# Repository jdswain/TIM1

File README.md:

# TIM1
Hardware files for 6504 based TIM-1 board.

This is a PCB for the Rockwell or MOS TIM-1 system.

More information can be found on <a href="https://swain.nz/micro">my website.</a>

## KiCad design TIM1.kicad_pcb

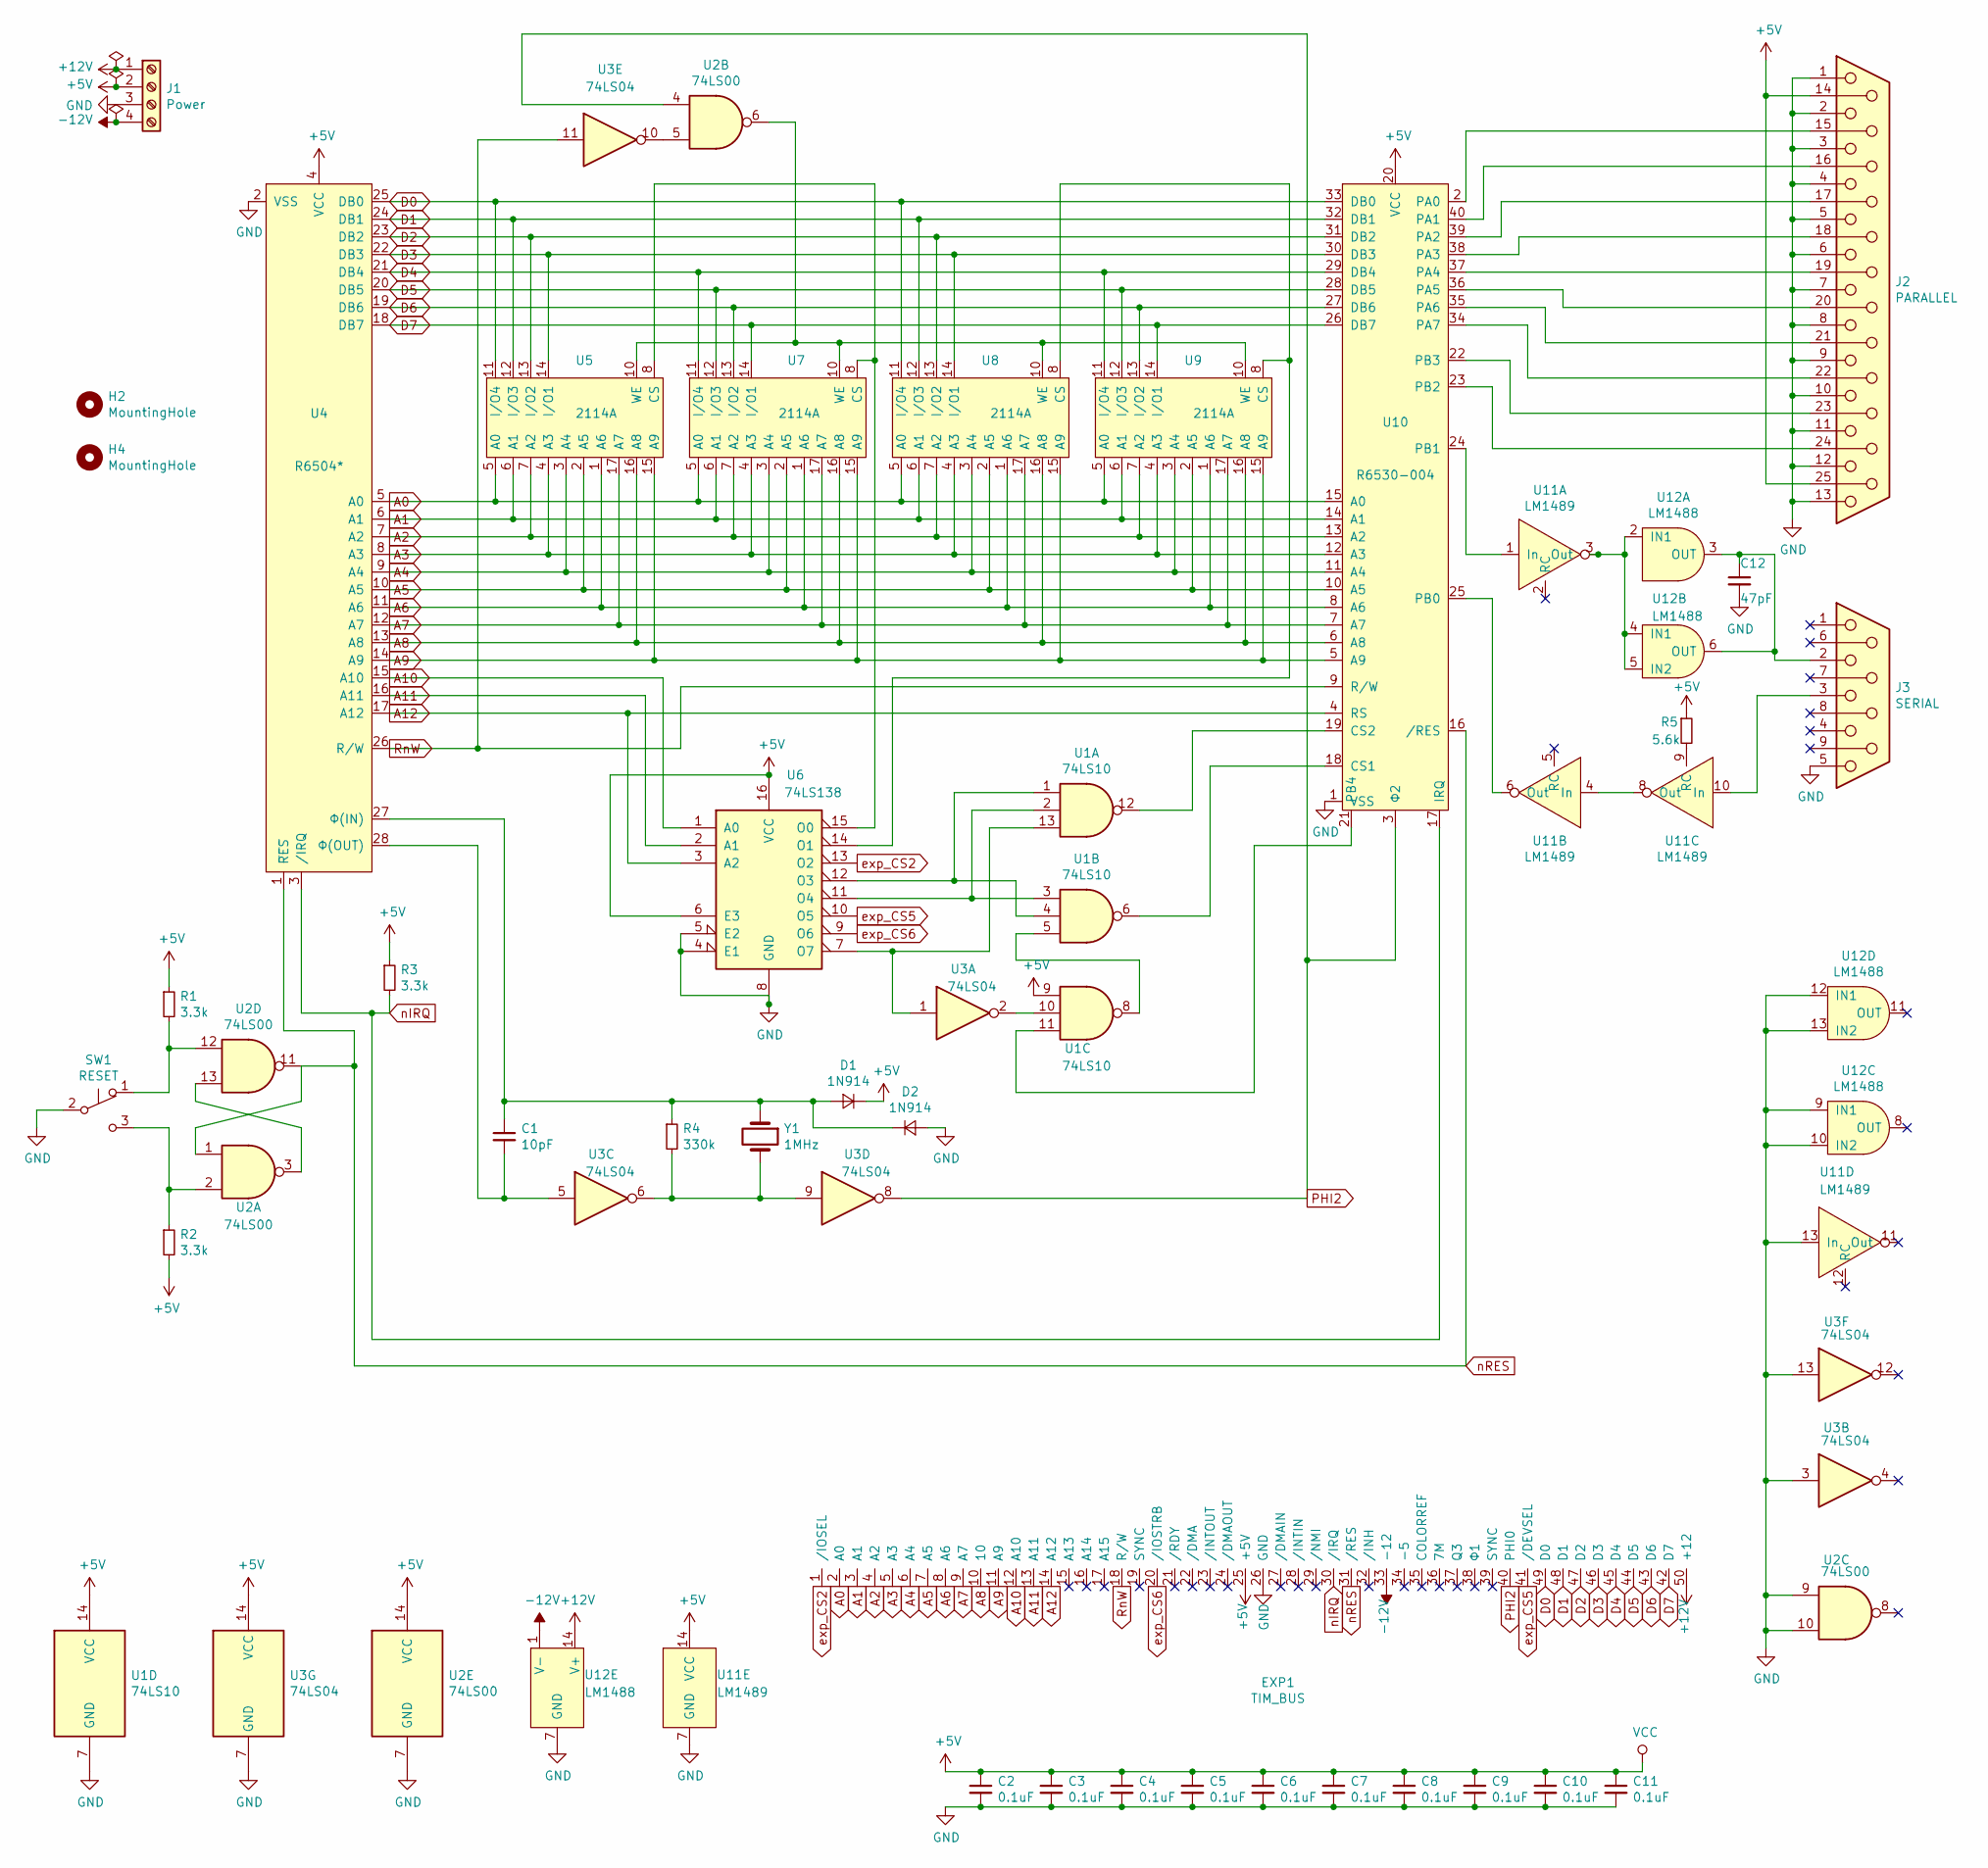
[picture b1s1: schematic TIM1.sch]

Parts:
C1: 10pF; C_Axial_L3.8mm_D2.6mm_P10.00mm_Horizontal
C2, C3, C4, C5, C6, C7, C8, C9, C10, C11: 0.1uF; C_Axial_L3.8mm_D2.6mm_P10.00mm_Horizontal
C12: 47pF; C_Axial_L3.8mm_D2.6mm_P10.00mm_Horizontal
D1, D2: 1N914; D_DO-15_P10.16mm_Horizontal
EXP1: TIM_BUS; EDGE_50
H2, H4: MountingHole; MountingHole_2.5mm
J1: Power; TerminalBlock_RND_205-00069_1x04_P7.50mm_Horizontal
J2: PARALLEL; DSUB-25_Male_Horizontal_P2.77x2.84mm_EdgePinOffset4.94mm_Ho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
J3: SERIAL; DSUB-9_Female_Horizontal_P2.77x2.84mm_EdgePinOffset4.94mm_H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
R1, R2, R3: 3.3k; R_Axial_DIN0207_L6.3mm_D2.5mm_P10.16mm_Horizontal
R4: 330k; R_Axial_DIN0207_L6.3mm_D2.5mm_P10.16mm_Horizontal
R5: 5.6k; R_Axial_DIN0207_L6.3mm_D2.5mm_P10.16mm_Horizontal
SW1: RESET; PB86-A0
U1: 74LS10; DIP-14_W7.62mm_Socket_LongPads
U2: 74LS00; DIP-14_W7.62mm_Socket_LongPads
U3: 74LS04; DIP-14_W7.62mm_Socket_LongPads
U4: R6504*; DIP-28_W15.24mm_Socket_LongPads
U5, U7, U8, U9: 2114A; DIP-18_W7.62mm_Socket_LongPads
U6: 74LS138; DIP-16_W7.62mm_Socket_LongPads
U10: R6530-004; DIP-40_W15.24mm_Socket_LongPads
U11: LM1489; DIP-14_W7.62mm_Socket_LongPads
U12: LM1488; DIP-14_W7.62mm_Socket_LongPads
Y1: 1MHz; Crystal_HC49-U_Horizontal

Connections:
+5V: C2.1, C3.1, C4.1, C5.1, C6.1, C7.1, C8.1, C9.1, C10.1, C11.1, D1.1 (K), EXP1.25 (+5V), J1.2, J2.14, J2.25, R1.1, R2.2, R3.1, R5.1, U1.9, U1.14 (VCC), U2.14 (VCC), U3.14 (VCC), U4.4 (VCC), U5.18 (VCC), U6.6 (E3), U6.16 (VCC), U7.18 (VCC), U8.18 (VCC), U9.18 (VCC), U10.20 (VCC), U11.14 (VCC)
+12V: EXP1.50 (+12), J1.1, U12.14 (V+)
-12V: EXP1.33 (-12), J1.4, U12.1 (V-)
A0: EXP1.2 (A0), U4.5 (A0), U5.5 (A0), U7.5 (A0), U8.5 (A0), U9.5 (A0), U10.15 (A0)
A1: EXP1.3 (A1), U4.6 (A1), U5.6 (A1), U7.6 (A1), U8.6 (A1), U9.6 (A1), U10.14 (A1)
A2: EXP1.4 (A2), U4.7 (A2), U5.7 (A2), U7.7 (A2), U8.7 (A2), U9.7 (A2), U10.13 (A2)
A3: EXP1.5 (A3), U4.8 (A3), U5.4 (A3), U7.4 (A3), U8.4 (A3), U9.4 (A3), U10.12 (A3)
A4: EXP1.6 (A4), U4.9 (A4), U5.3 (A4), U7.3 (A4), U8.3 (A4), U9.3 (A4), U10.11 (A4)
A5: EXP1.7 (A5), U4.10 (A5), U5.2 (A5), U7.2 (A5), U8.2 (A5), U9.2 (A5), U10.10 (A5)
A6: EXP1.8 (A6), U4.11 (A6), U5.1 (A6), U7.1 (A6), U8.1 (A6), U9.1 (A6), U10.8 (A6)
A7: EXP1.9 (A7), U4.12 (A7), U5.17 (A7), U7.17 (A7), U8.17 (A7), U9.17 (A7), U10.7 (A7)
A8: EXP1.10, U4.13 (A8), U5.16 (A8), U7.16 (A8), U8.16 (A8), U9.16 (A8), U10.6 (A8)
A9: EXP1.11 (A9), U4.14 (A9), U5.15 (A9), U7.15 (A9), U8.15 (A9), U9.15 (A9), U10.5 (A9)
A10: EXP1.12 (A10), U4.15 (A10), U6.1 (A0)
A11: EXP1.13 (A11), U4.16 (A11), U6.2 (A1)
A12: EXP1.14 (A12), U4.17 (A12), U6.3 (A2), U10.4 (RS)
D0: EXP1.49 (D0), U4.25 (DB0), U5.11 (I/O4), U8.11 (I/O4), U10.33 (DB0)
D1: EXP1.48 (D1), U4.24 (DB1), U5.12 (I/O3), U8.12 (I/O3), U10.32 (DB1)
D2: EXP1.47 (D2), U4.23 (DB2), U5.13 (I/O2), U8.13 (I/O2), U10.31 (DB2)
D3: EXP1.46 (D3), U4.22 (DB3), U5.14 (I/O1), U8.14 (I/O1), U10.30 (DB3)
D4: EXP1.45 (D4), U4.21 (DB4), U7.11 (I/O4), U9.11 (I/O4), U10.29 (DB4)
D5: EXP1.44 (D5), U4.20 (DB5), U7.12 (I/O3), U9.12 (I/O3), U10.28 (DB5)
D6: EXP1.43 (D6), U4.19 (DB6), U7.13 (I/O2), U9.13 (I/O2), U10.27 (DB6)
D7: EXP1.42 (D7), U4.18 (DB7), U7.14 (I/O1), U9.14 (I/O1), U10.26 (DB7)
GND: C2.2, C3.2, C4.2, C5.2, C6.2, C7.2, C8.2, C9.2, C10.2, C11.2, C12.2, D2.2 (A), EXP1.26 (GND), J1.3, J2.1, J2.2, J2.3, J2.4, J2.5, J2.6, J2.7, J2.8, J2.9, J2.10, J2.11, J2.12, J2.13, J3.5, SW1.2 (B), U1.7 (GND), U2.7 (GND), U2.9, U2.10, U3.3, U3.7 (GND), U3.13, U4.2 (VSS), U5.9 (GND), U6.4 (E1), U6.5 (E2), U6.8 (GND), U7.9 (GND), U8.9 (GND), U9.9 (GND), U10.1 (VSS), U11.7 (GND), U11.13 (In), U12.7 (GND), U12.9 (IN1), U12.10 (IN2), U12.12 (IN1), U12.13 (IN2)
unnamed: C1.1, D1.2 (A), D2.1 (K), R4.1, U4.27 (Φ(IN)), Y1.1
unnamed: C1.2, U3.5, U4.28 (Φ(OUT))
unnamed: C12.1, J3.2, U12.3 (OUT), U12.6 (OUT)
unnamed: J2.15, U10.2 (PA0)
unnamed: J2.16, U10.40 (PA1)
unnamed: J2.17, U10.39 (PA2)
unnamed: J2.18, U10.38 (PA3)
unnamed: J2.19, U10.37 (PA4)
unnamed: J2.20, U10.36 (PA5)
unnamed: J2.21, U10.35 (PA6)
unnamed: J2.22, U10.34 (PA7)
unnamed: J2.23, U10.22 (PB3)
unnamed: J2.24, U10.23 (PB2)
unnamed: J3.3, U11.10 (In)
unnamed: R1.2, SW1.1 (A), U2.12
unnamed: R2.1, SW1.3 (C), U2.2
unnamed: R4.2, U3.6, U3.9, Y1.2
unnamed: R5.2, U11.9 (RC)
unnamed: U1.1, U1.4, U6.12 (O3)
unnamed: U1.2, U1.3, U6.11 (O4)
unnamed: U1.5, U1.8
unnamed: U1.6, U10.18 (CS1)
unnamed: U1.10, U3.2
unnamed: U1.11, U10.21 (PB4)
unnamed: U1.12, U10.19 (CS2)
unnamed: U1.13, U3.1, U6.7 (O7)
unnamed: U2.5, U3.10
unnamed: U2.6, U5.10 (WE), U7.10 (WE), U8.10 (WE), U9.10 (WE)
unnamed: U2.3, U2.13
unnamed: U5.8 (CS), U6.15 (O0), U7.8 (CS)
unnamed: U6.14 (O1), U8.8 (CS), U9.8 (CS)
unnamed: U10.24 (PB1), U11.1 (In)
unnamed: U10.25 (PB0), U11.6 (Out)
unnamed: U11.3 (Out), U12.2 (IN1), U12.4 (IN1), U12.5 (IN2)
unnamed: U11.4 (In), U11.8 (Out)
PHI2: EXP1.40 (PHI0), U2.4, U3.8, U10.3 (Φ2)
RnW: EXP1.18 (R/W), U3.11, U4.26 (R/W), U10.9 (R/W)
exp_CS2: EXP1.1 (/IOSEL), U6.13 (O2)
exp_CS5: EXP1.41 (/DEVSEL), U6.10 (O5)
exp_CS6: EXP1.20 (/IOSTRB), U6.9 (O6)
nIRQ: EXP1.30 (/IRQ), R3.2, U4.3 (/IRQ), U10.17 (IRQ)
nRES: EXP1.31 (/RES), U2.1, U2.11, U4.1 (R̅E̅S̅), U10.16 (/RES)

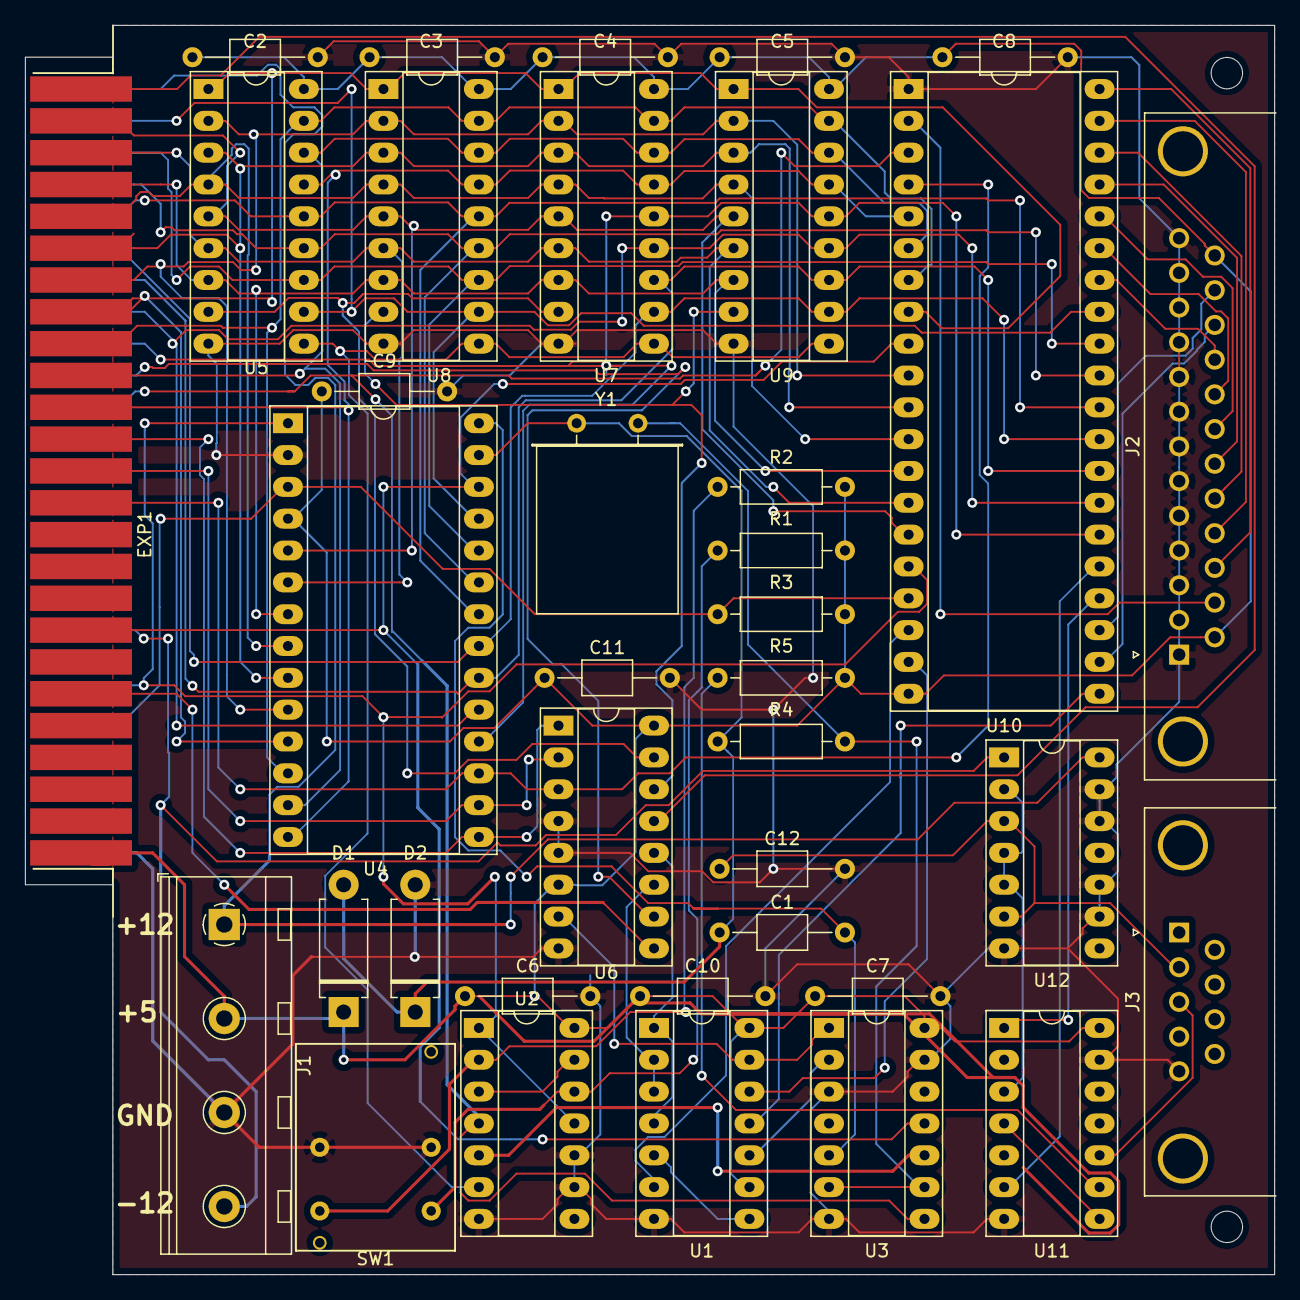
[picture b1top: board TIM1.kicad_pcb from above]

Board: 2 copper layers, 99.7 x 99.7 mm, 39 parts (0 on the bottom side), 67 nets.

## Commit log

2021-03-04 Updated with fixes from first board
2021-03-04 Update readme.
